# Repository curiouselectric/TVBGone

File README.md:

# TV-B-Gone
This TV-B-Gone kit is a 'disruptive technology device' designed to switch off annoying and unnecessary televisions.

The TV-B-Gone was conceived by hack-hero Mitch Altman. It is designed emit the 'OFF' code for the majority of TVs in Europe and the US. Basically it is a TV remote control which only has the power button. It is designed to turn off inappropriate TVs, such as unwatched ones in public spaces. It is a commercial product, but Mitch has also worked with Adafruit industries to have an open-source design.

You can buy this as a kit of parts in the UK [from the Curious Electric Company](https://www.curiouselectric.co.uk/collections/featured/products/tv-b-gone).

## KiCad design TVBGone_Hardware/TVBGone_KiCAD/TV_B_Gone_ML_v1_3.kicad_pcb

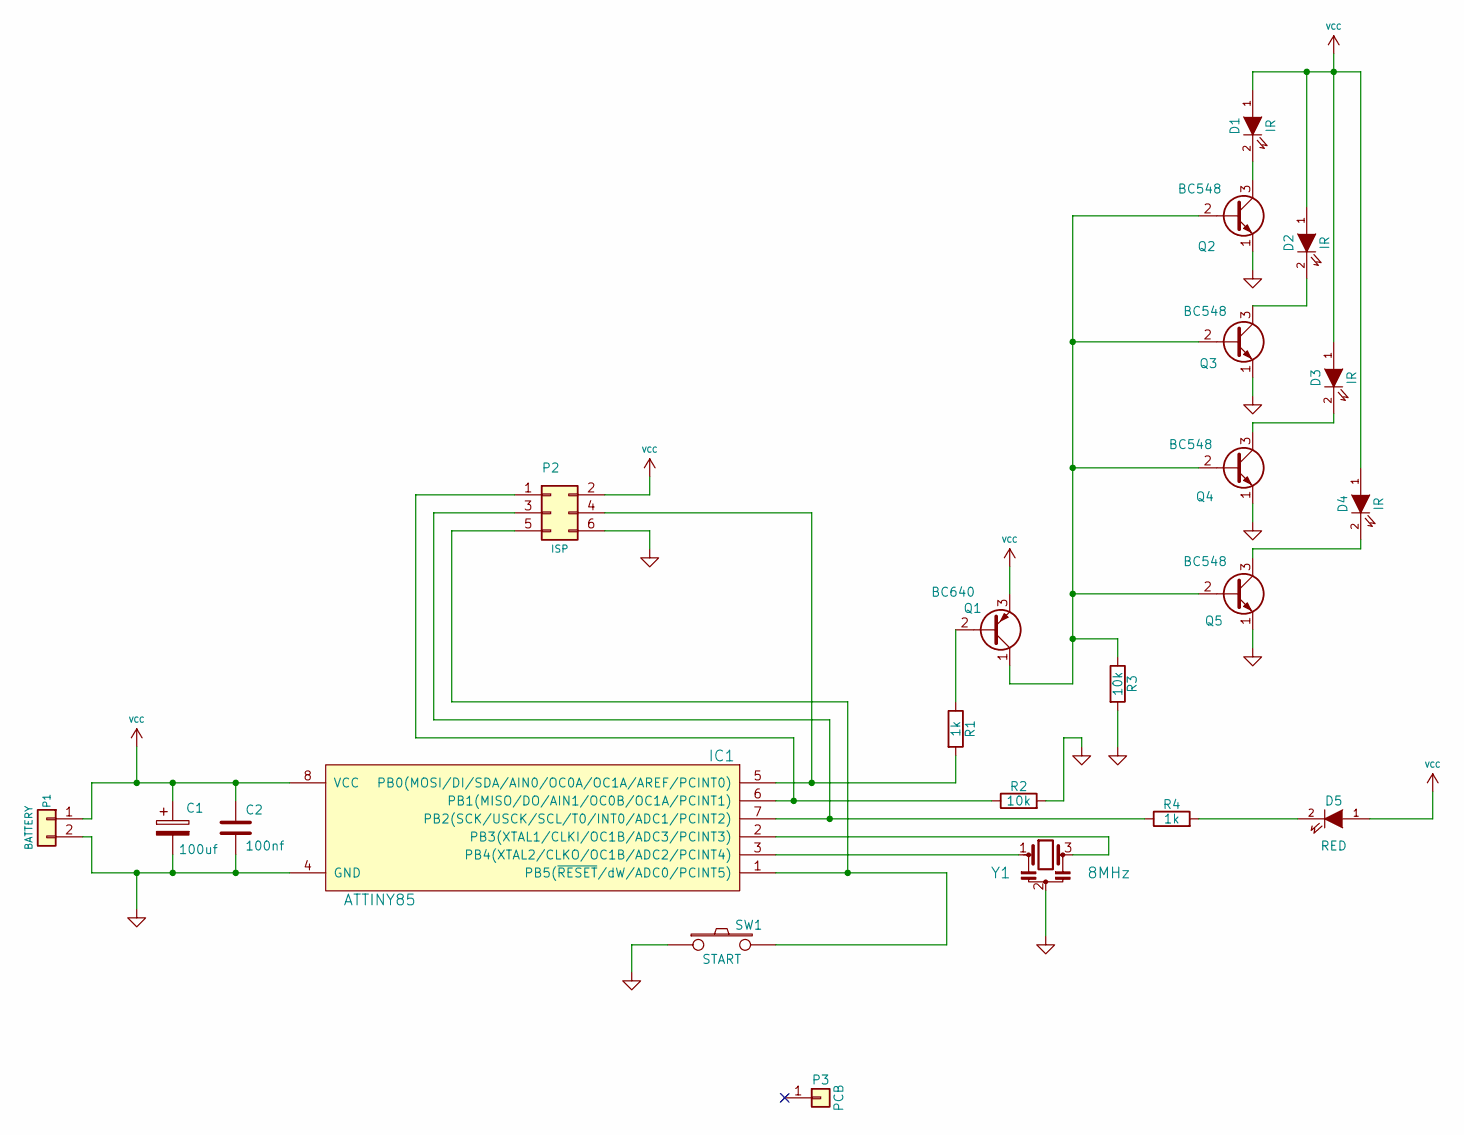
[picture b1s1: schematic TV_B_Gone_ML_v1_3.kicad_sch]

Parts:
C1: 100uf; C_1V7_TH
C2: 100nf; C1_wide_lg_pad
D1, D2, D3, D4: IR; LED-5MM_larg_pad
D5: RED; LED-5MM_larg_pad
IC1: ATTINY85; DIP-8__300_ELL
P1: BATTERY; Batt_Connector_Strain_Relief
P2: ISP; TH3x2_ISP
P3: PCB; TV_B_Gone_ML_v1_3_PCB
Q1: BC640; TO-92_Inline
Q2, Q3, Q4, Q5: BC548; TO92-EBC_large_pad
R1, R4: 1k; TH_Resistor_1
R2, R3: 10k; TH_Resistor_1
SW1: START; SW_PUSH_SMALL_lg_pad
Y1: 8MHz; SIL-3_lg_pad

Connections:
GND: C1.2, C2.2, IC1.4 (GND), P1.2, P2.6, Q2.1 (E), Q3.1 (E), Q4.1 (E), Q5.1 (E), R2.2, R3.2, SW1.1, Y1.2
unnamed: D1.2 (K), Q2.3 (C)
unnamed: D2.2 (K), Q3.3 (C)
unnamed: D3.2 (K), Q4.3 (C)
unnamed: D4.2 (K), Q5.3 (C)
unnamed: D5.2 (K), R4.2
unnamed: IC1.1 (PB5(~RESET/dW/ADC0/PCINT5)), P2.5, SW1.2
unnamed: IC1.2 (PB3(XTAL1/CLKI/OC1B/ADC3/PCINT3)), Y1.3
unnamed: IC1.3 (PB4(XTAL2/CLKO/OC1B/ADC2/PCINT4)), Y1.1
unnamed: IC1.5 (PB0(MOSI/DI/SDA/AIN0/OC0A/OC1A/AREF/PCI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), P2.4, R1.2
unnamed: IC1.6 (PB1(MISO/DO/AIN1/OC0B/OC1A/PCINT1)), P2.1, R2.1
unnamed: IC1.7 (PB2(SCK/USCK/SCL/T0/INT0/ADC1/PCINT2)), P2.3, R4.1
unnamed: Q1.1 (C), Q2.2 (B), Q3.2 (B), Q4.2 (B), Q5.2 (B), R3.1
unnamed: Q1.2 (B), R1.1
VCC: C1.1, C2.1, D1.1 (A), D2.1 (A), D3.1 (A), D4.1 (A), D5.1 (A), IC1.8 (VCC), P1.1, P2.2, Q1.3 (E)

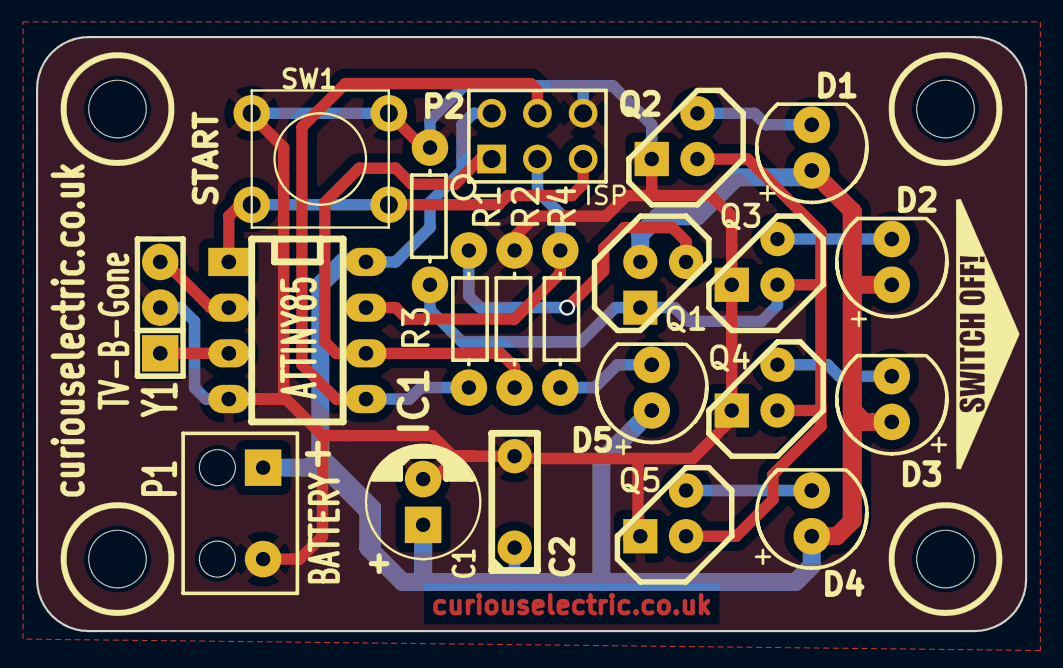
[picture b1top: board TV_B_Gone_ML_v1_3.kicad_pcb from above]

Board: 2 copper layers, 54.9 x 33.0 mm, 22 parts (0 on the bottom side), 15 nets.

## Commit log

2015-10-29 Initial Commit of version 1
    This is the original TV-B-Gone version.
2015-10-29 New Design PCB - with Mounting Holes
    Totally re-done PCB and footprint files
2016-03-18 Added new instructions
2017-02-13 Uploading Images for instructions
2017-02-17 Added new photos
2017-02-17 Images uploads
2017-02-18 New Images
2017-02-18 Change images
2017-02-19 Updated for Dillinger.io use
2017-02-19 Changed for Dillinger.io
2017-03-19 Small update
2017-03-20 Added rst file
2018-12-30 Slight changes to instructions
2018-12-30 Updated PCB files
2022-01-19 Updated Instructions
    Added transistor orientation. Added svg for instruction files
2022-05-10 PCB redone_v1_3
2022-05-27 Updated PCB and Instructions
2025-03-19 Updates to Kicad 9 and sorted schematic
2025-03-19 Updated removed lock file
